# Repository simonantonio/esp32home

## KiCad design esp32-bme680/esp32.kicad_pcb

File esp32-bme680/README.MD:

# NOTES
ESP32-C3 Super Mini - with support for AM2302 or BME680 sensors  

For monitoring humidity, pressure, tempurature, gas* (VOX)

**BME only*

## ESP32Home Config
[yaml](esp32home.yaml)

## Rendering

## ESP32-C3 Super Mini Pin Mappings

## Errata
Fucked up ic2 config - pinout is swapped wrong  

|Function|GPIO Pin|
|----|---|
|sda| "GPIO9"|
|scl| "GPIO8"|

### TO FIX
* USB to be off the edge of the board
* pinout to be fixed
* add pin labels for esp32 pins
* pretty sure i got the esp32 footprint up the wrong way
* esp32 footprint - to convert to single side no drill.

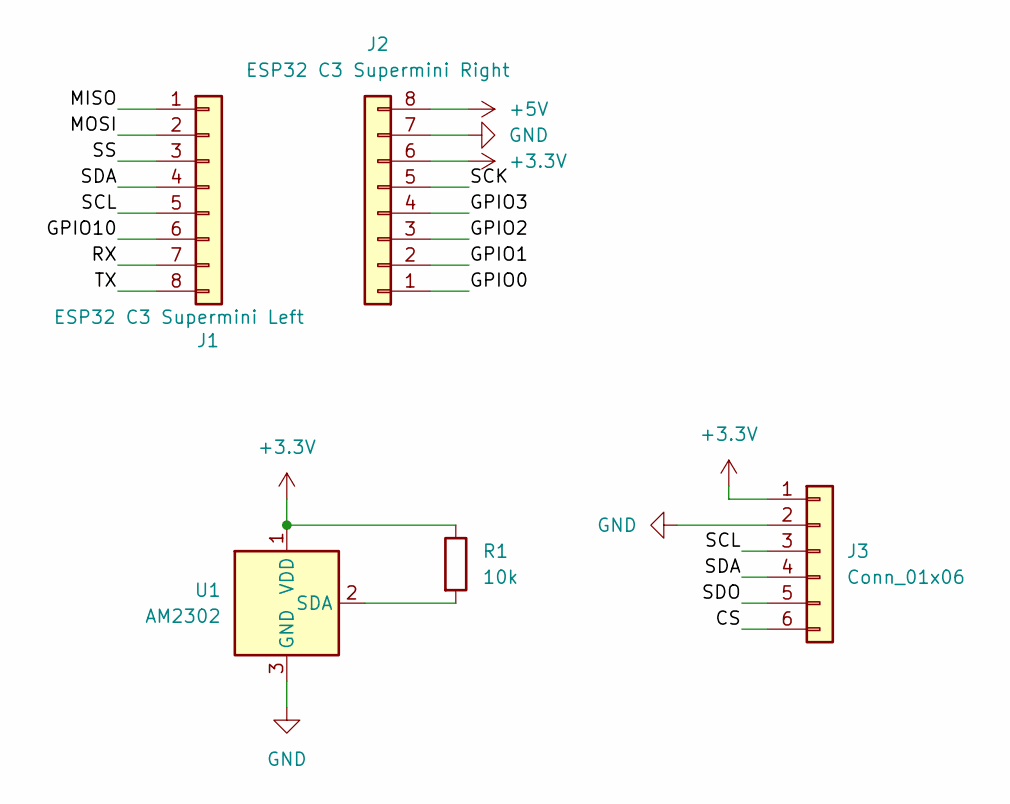
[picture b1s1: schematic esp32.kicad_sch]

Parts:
J1: ESP32 C3 Supermini Left; PinHeader_1x08_P2.54mm_Vertical
J2: ESP32 C3 Supermini Right; PinHeader_1x08_P2.54mm_Vertical
J3: Conn_01x06; PinSocket_1x06_P2.54mm_Vertical
R1: 10k; R_Axial_DIN0207_L6.3mm_D2.5mm_P10.16mm_Horizontal
U1: AM2302; ASAIR_AM2302_P2.54mm_Vertical

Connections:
+3.3V: J2.6, J3.1, R1.1, U1.1 (VDD)
+5V: J2.8
/CS: J3.6
/GPIO0: J2.1
/GPIO1: J2.2
/GPIO2: J2.3
/GPIO3: J2.4
/GPIO10: J1.6
/MISO: J1.1
/MOSI: J1.2
/RX: J1.7
/SCK: J2.5
/SCL: J1.5, J3.3
/SDA: J1.4, J3.4
/SDO: J3.5
/SS: J1.3
/TX: J1.8
GND: J2.7, J3.2, U1.3 (GND), U1.4 (GND)
unnamed: R1.2, U1.2 (SDA)

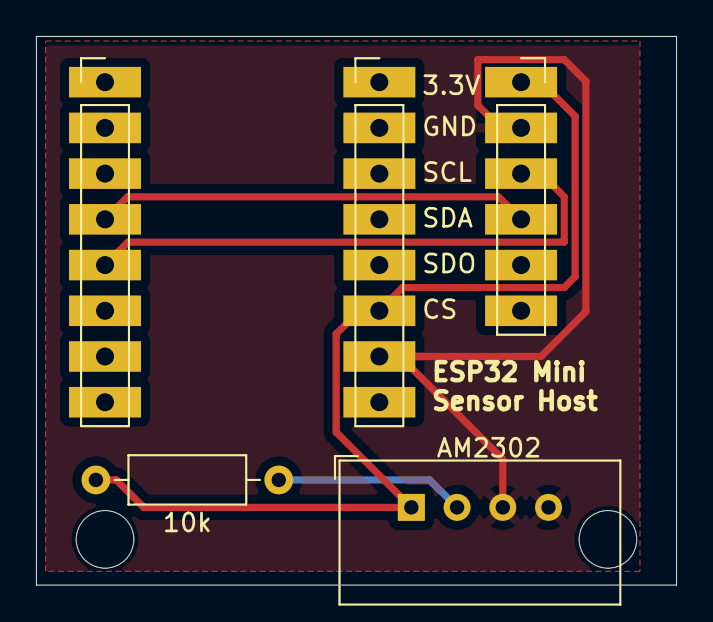
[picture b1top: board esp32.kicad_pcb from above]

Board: 2 copper layers, 35.6 x 30.5 mm, 5 parts (0 on the bottom side), 5 nets.

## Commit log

2025-02-16 first set of sensors for esp32home
    remove bad
